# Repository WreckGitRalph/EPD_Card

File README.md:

# EPD_Card

A KiCAD project for implementing a fun, interactive business card or nametag. 
The design incorporates a Good-Display GDEM0154E97LT ePaper display and a simple capacitive touch pad, and is powered by a CR1216 coin battery. ICSP connections are broken out for easy reprogramming.

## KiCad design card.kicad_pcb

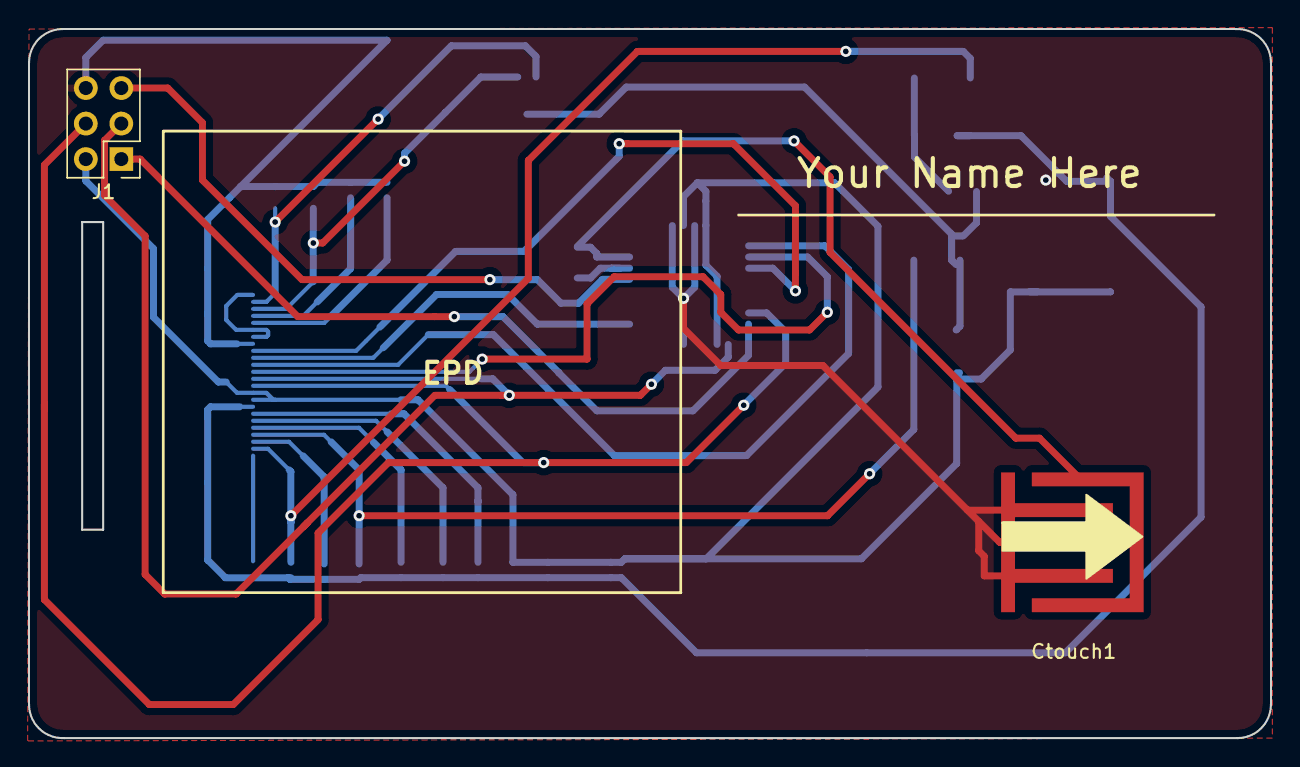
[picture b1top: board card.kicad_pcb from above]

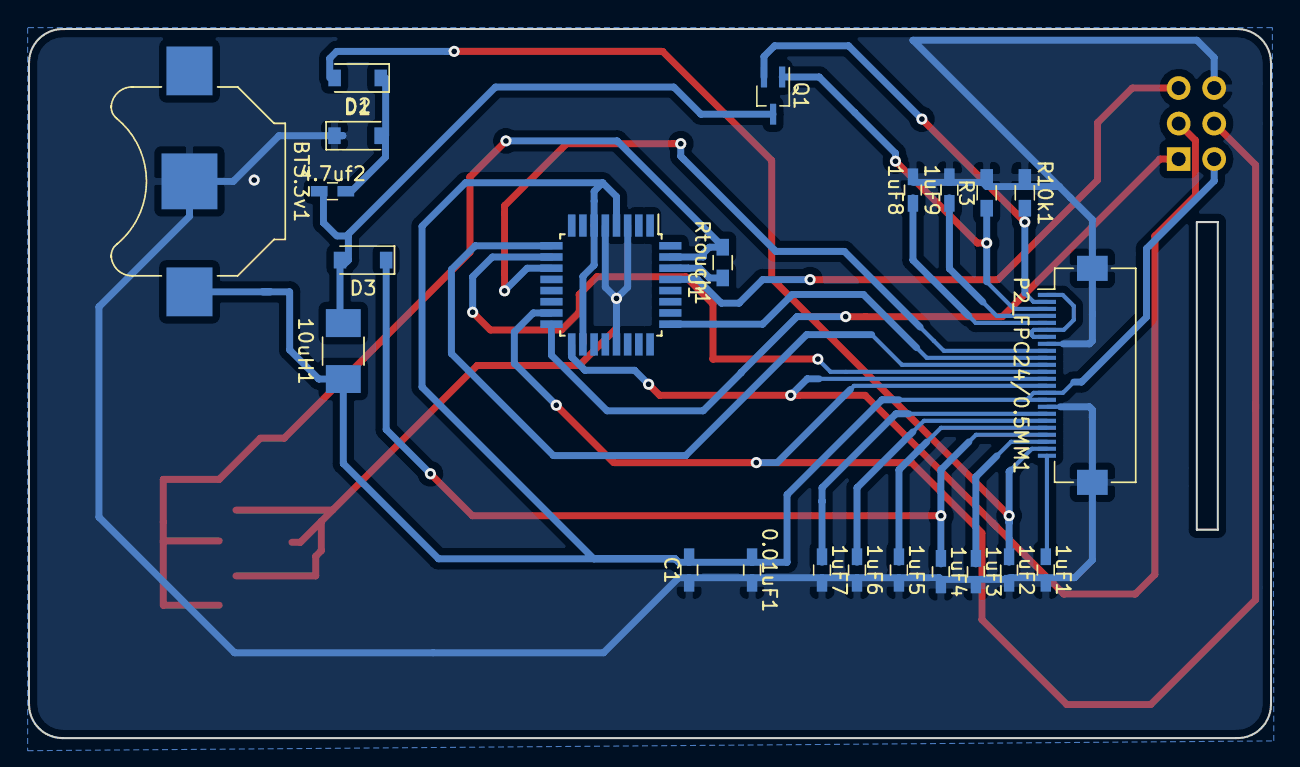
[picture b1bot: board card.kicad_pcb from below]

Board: 2 copper layers, 88.8 x 50.7 mm, 25 parts (23 on the bottom side), 26 nets.

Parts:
0.01uF1, 1uF1, 1uF2, 1uF3, 1uF4, 1uF5, 1uF6, 1uF7, 1uF8, 1uF9, 4.7uf2: C; C_0603_HandSoldering
10uH1: L; L_1210_HandSoldering
BT3.3v1: Battery_Cell; Keystone_3000_1x12mm-CoinCell
C1: 4.7uf1; C_0603_HandSoldering
Ctouch1: C; Touchpad
D1, D2, D3: D; D_SOD-123
J1: Conn_02x03_Odd_Even; Pin_Header_Straight_2x03_Pitch2.54mm
P2_FPC24/0.5MM1: Conn_01x24_Male; Hirose_FH12-24S-0.5SH_1x24_P0.50mm_Horizontal_Gnd17_Mirr
Q1: Si1308EDL; SOT-323_SC-70_Handsoldering
R3, R10k1: R; R_0603_HandSoldering
Rtouch1: 1M; R_0603_HandSoldering
U1: ATMEGA168PA-AU; TQFP-32_7x7mm_Pitch0.8mm

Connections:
/BUSY: P2_FPC24/0.5MM1.9, U1.11
/CS: P2_FPC24/0.5MM1.12, U1.10
/DC: P2_FPC24/0.5MM1.11, U1.9
/GDR: P2_FPC24/0.5MM1.2, Q1.2, R10k1.2
/PREVGH: 1uF4.1, D3.1, P2_FPC24/0.5MM1.21
/PREVGL: 1uF2.1, D2.2, P2_FPC24/0.5MM1.23
/RES: P2_FPC24/0.5MM1.10, U1.25
/RESE: P2_FPC24/0.5MM1.3, Q1.1, R3.1
/SCLK: J1.3, P2_FPC24/0.5MM1.13, U1.17
/SDI: J1.4, P2_FPC24/0.5MM1.14, U1.15
GND: 0.01uF1.2, 1uF1.2, 1uF2.2, 1uF3.2, 1uF4.2, 1uF5.2, 1uF6.2, 1uF7.2, 1uF8.2, 1uF9.2, BT3.3v1.2, C1.1, Ctouch1.2, D1.1, J1.6, P2_FPC24/0.5MM1.8, P2_FPC24/0.5MM1.17, R3.2, R10k1.1, U1.3, U1.5, U1.21
unnamed: 0.01uF1.1, 10uH1.1, BT3.3v1.1, C1.2, J1.2, P2_FPC24/0.5MM1.15, P2_FPC24/0.5MM1.16, U1.4, U1.6, U1.18
unnamed: 1uF1.1, P2_FPC24/0.5MM1.24
unnamed: 1uF3.1, P2_FPC24/0.5MM1.22
unnamed: 1uF5.1, P2_FPC24/0.5MM1.20
unnamed: 1uF6.1, P2_FPC24/0.5MM1.19
unnamed: 1uF7.1, P2_FPC24/0.5MM1.18
unnamed: 1uF8.1, P2_FPC24/0.5MM1.5
unnamed: 1uF9.1, P2_FPC24/0.5MM1.4
unnamed: 4.7uf2.2, D1.2, D2.1
unnamed: 4.7uf2.1, 10uH1.2, D3.2, Q1.3
unnamed: Ctouch1.1, Rtouch1.2, U1.31
unnamed: J1.1, U1.16
unnamed: J1.5, U1.29
unnamed: P2_FPC24/0.5MM1.1, P2_FPC24/0.5MM1.6, P2_FPC24/0.5MM1.7
unnamed: Rtouch1.1, U1.30

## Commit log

2018-04-25 added front and back 3D renderings
2018-05-02 fixed FPC connector footprint, updated traces
2018-07-06 increased some footprint sizes, added missing via
2018-08-21 Connected display reset to AVR, increased inductor footprint size.
